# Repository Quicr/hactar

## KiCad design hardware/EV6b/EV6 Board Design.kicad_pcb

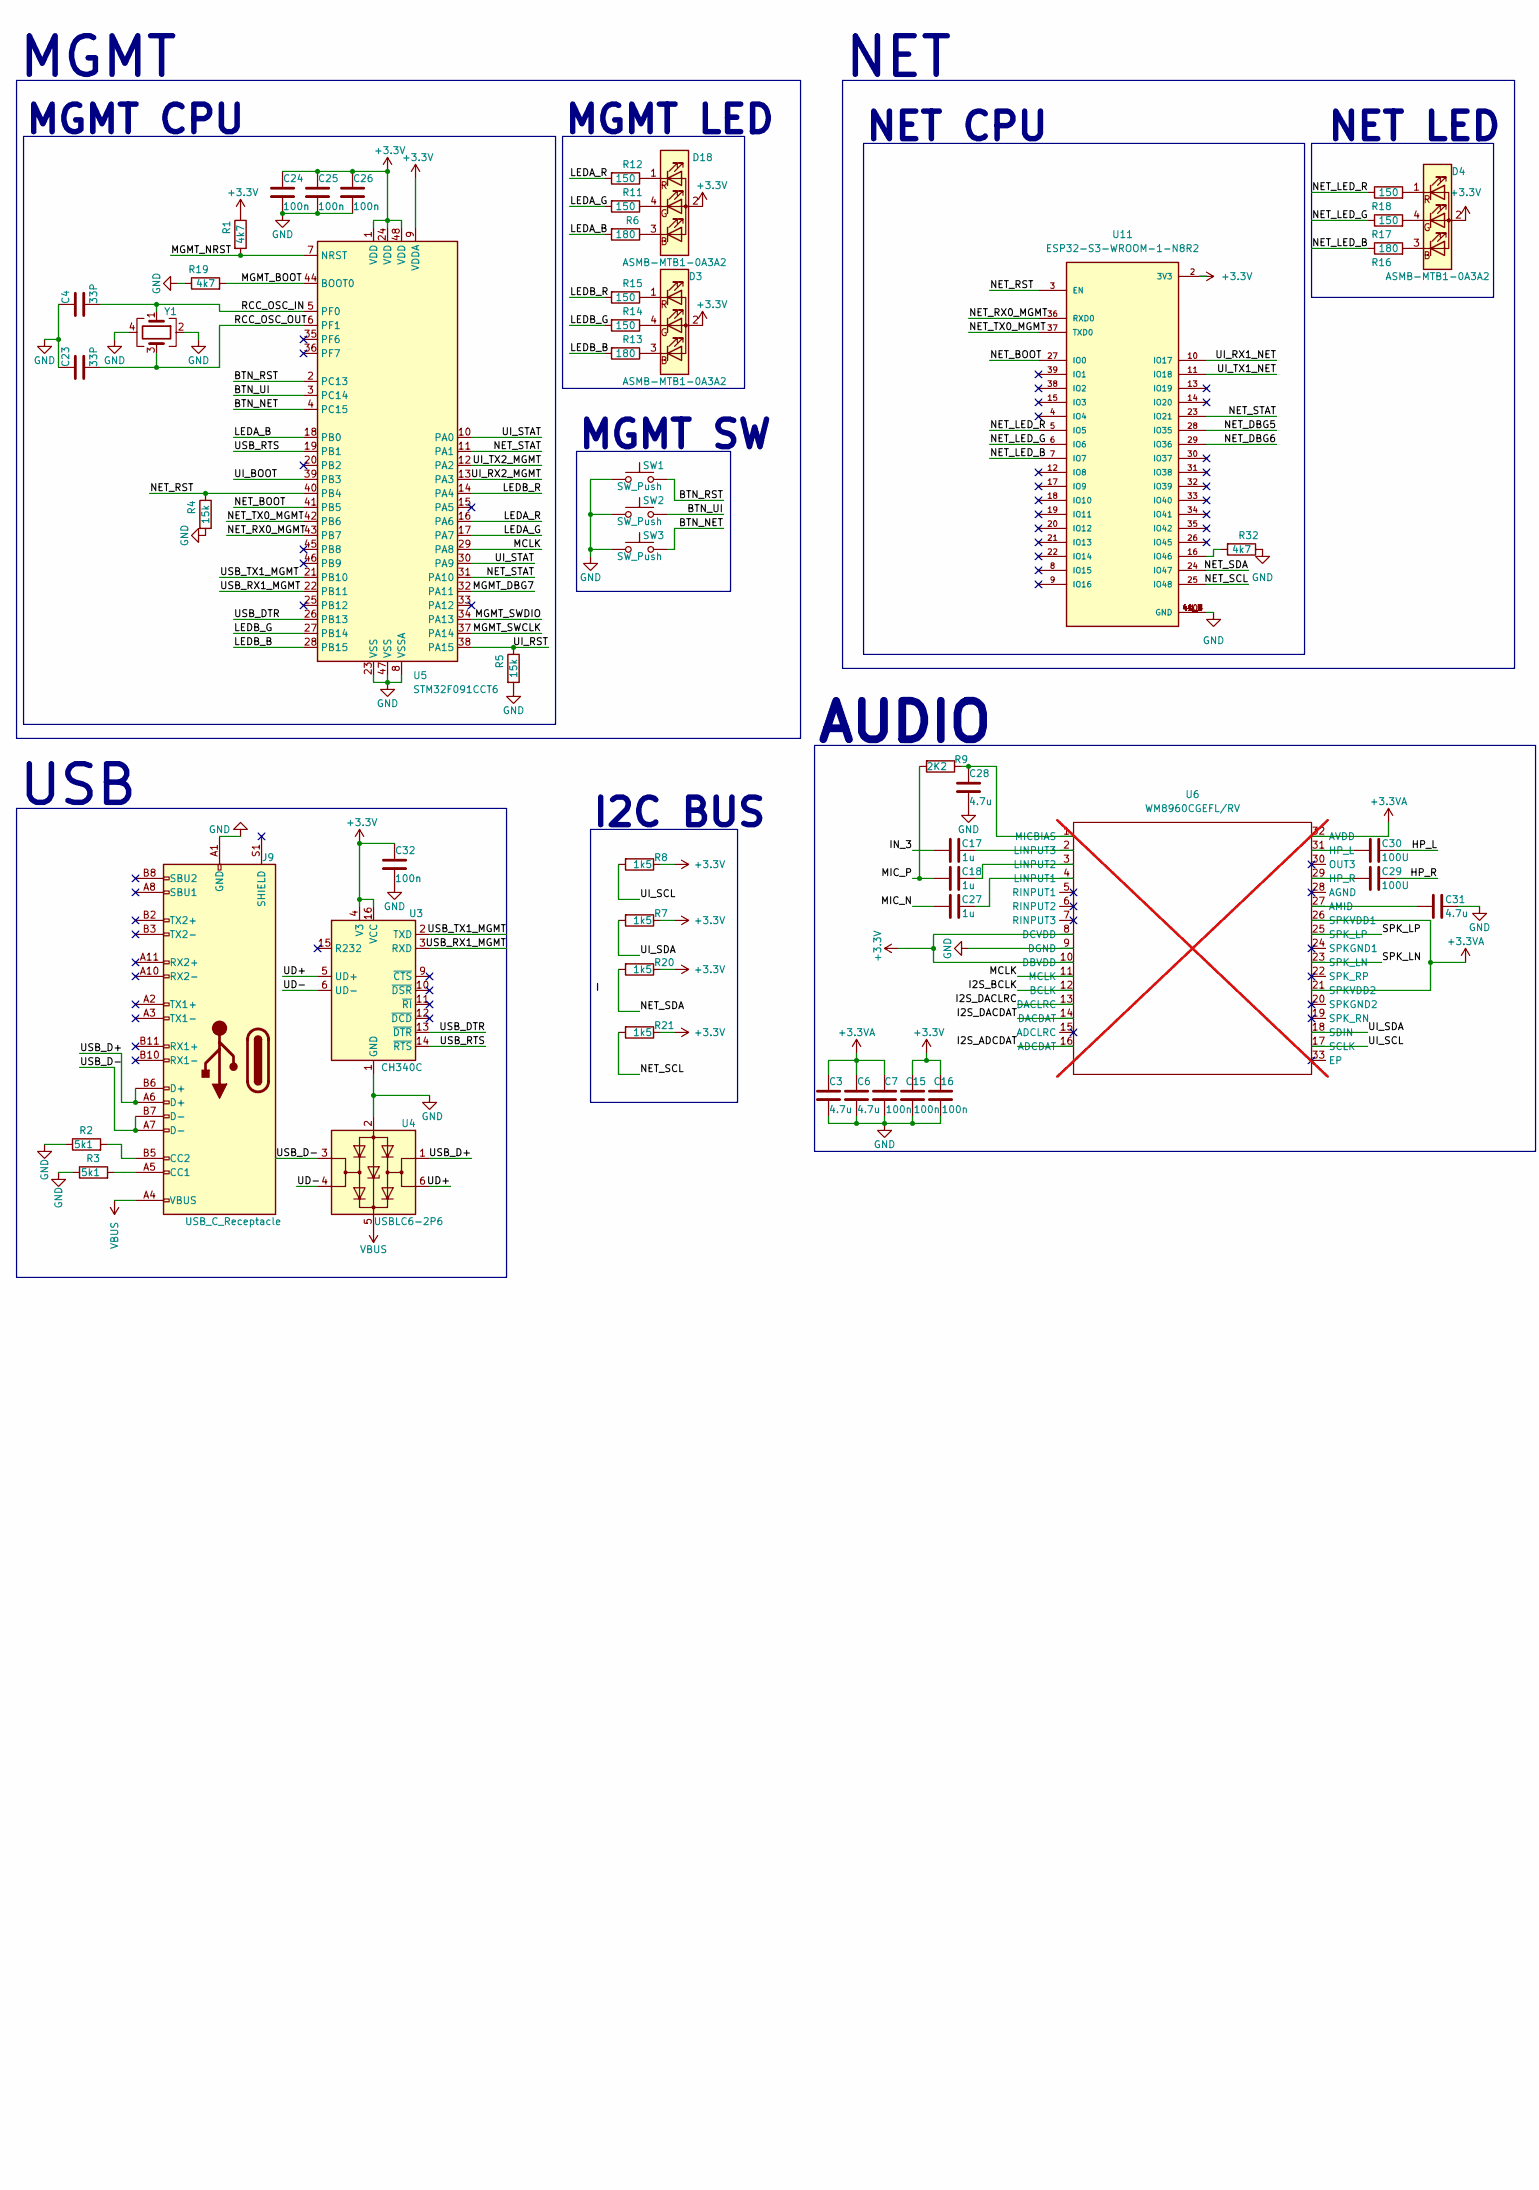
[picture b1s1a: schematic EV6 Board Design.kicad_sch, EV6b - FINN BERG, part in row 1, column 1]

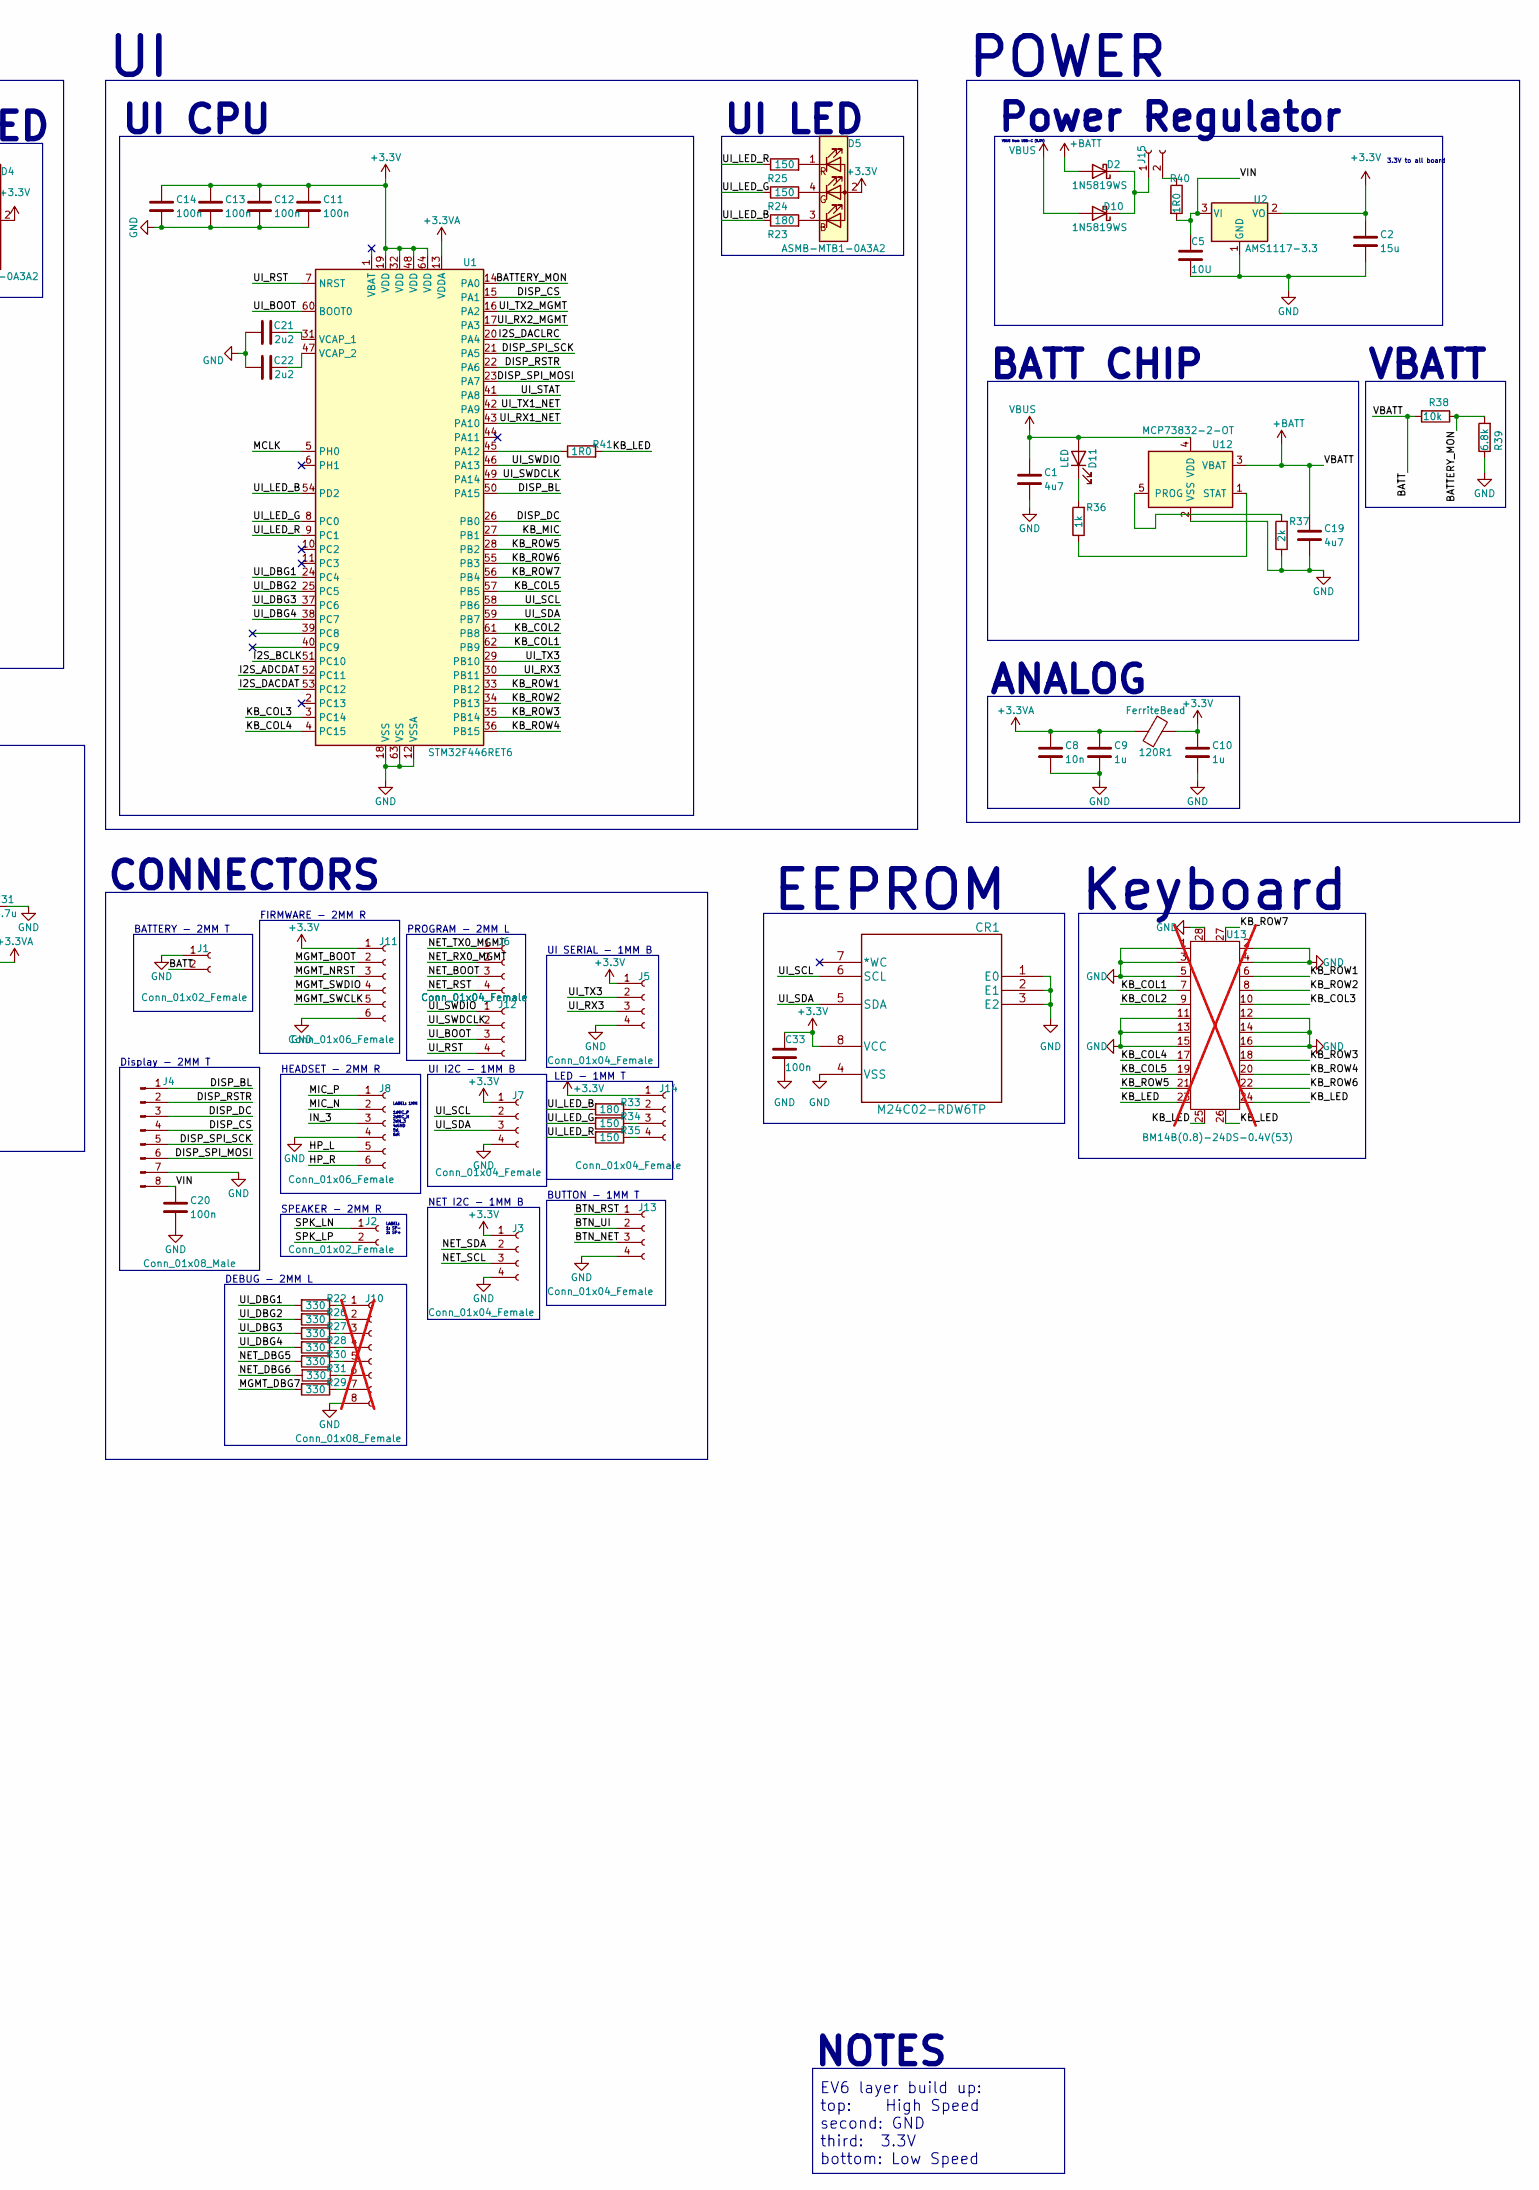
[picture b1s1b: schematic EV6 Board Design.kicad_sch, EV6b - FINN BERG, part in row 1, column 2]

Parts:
120R1: FerriteBead; L_0603_1608Metric
C1, C19: 4u7; C_0402_1005Metric
C2: 15u; C_0402_1005Metric
C3, C6, C28, C31: 4.7u; C_0402_1005Metric
C4, C23: 33P; C_0805_2012Metric
C5: 10U; C_0402_1005Metric
C7, C11, C12, C13, C14, C15, C16, C20, C24, C25, C26, C32, C33: 100n; C_0402_1005Metric
C8: 10n; C_0402_1005Metric
C9, C10, C17, C18, C27: 1u; C_0402_1005Metric
C21, C22: 2u2; C_0402_1005Metric
C29, C30: 100U; C_1206_3216Metric
CR1: M24C02-RDW6TP; New_ESP32_M24C02-RMN6TP
D2, D10: 1N5819WS; D_SOD-323
D3, D4, D5, D18: ASMB-MTB1-0A3A2; LED RGB
D11: LED; LED_0805_2012Metric
J1, J2, J15: Conn_01x02_Female; JST_PH_S2B-PH-SM4-TB_1x02-1MP_P2.00mm_Horizontal
J3, J5, J6, J7, J12, J13, J14: Conn_01x04_Female; 1x4pin 1mm connector
J4: Conn_01x08_Male; PinHeader_1x08_P2.54mm_Vertical
J8, J11: Conn_01x06_Female; JST_PH_S6B-PH-SM4-TB_1x06-1MP_P2.00mm_Horizontal
J9: USB_C_Receptacle; USB_C_Receptacle_HRO_TYPE-C-31-M-12
J10: Conn_01x08_Female; JST_PH_S8B-PH-SM4-TB_1x08-1MP_P2.00mm_Horizontal; not fitted
R1, R19, R32: 4k7; R_0402_1005Metric
R2, R3: 5k1; R_0402_1005Metric
R4, R5: 15k; R_0402_1005Metric
R6, R13, R16, R23, R33: 180; R_0402_1005Metric
R7, R8, R20, R21: 1k5; R_0402_1005Metric
R9: 2K2; R_0402_1005Metric
R11, R12, R14, R15, R17, R18, R24, R25, R34, R35: 150; R_0402_1005Metric
R22, R26, R27, R28, R29, R30, R31: 330; R_0402_1005Metric
R36: 1k; R_0402_1005Metric
R37: 2k; R_0402_1005Metric
R38: 10k; R_0402_1005Metric
R39: 6.8k; R_0402_1005Metric
R40, R41: 1R0; R_0402_1005Metric
SW1, SW2, SW3: SW_Push; SW_DIP_SPSTx01_Slide_6.7x4.1mm_W6.73mm_P2.54mm_LowProfile_J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
U1: STM32F446RET6; LQFP-64_10x10mm_P0.5mm
U2: AMS1117-3.3; SOT-223-3_TabPin2
U3: CH340C; SOIC-16_3.9x9.9mm_P1.27mm
U4: USBLC6-2P6; SOT-666
U5: STM32F091CCT6; LQFP-48_7x7mm_P0.5mm; LCSC C129795
U6: WM8960CGEFL/RV; QFN50P500X500X90-33N; not fitted
U11: ESP32-S3-WROOM-1-N8R2; ESP32-S3-WROOM-1U
U12: MCP73832-2-OT; SOT-23-5
U13: BM14B(0.8)-24DS-0.4V(53); not fitted
Y1: Crystal_GND24; Crystal_SMD_3225-4Pin_3.2x2.5mm

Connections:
+3.3V: 120R1.2, C2.1, C10.1, C11.1, C12.1, C13.1, C14.1, C15.2, C16.2, C24.1, C25.1, C26.1, C32.1, C33.1, CR1.8 (VCC), D3.2 (A), D4.2 (A), D5.2 (A), D18.2 (A), J3.1, J5.1, J7.1, J11.1, J14.1, R1.1, R7.1, R8.1, R20.1, R21.1, U1.19 (VDD), U1.32 (VDD), U1.48 (VDD), U1.64 (VDD), U2.2 (VO), U3.4 (V3), U3.16 (VCC), U5.1 (VDD), U5.9 (VDDA), U5.24 (VDD), U5.48 (VDD), U6.8 (DCVDD), U6.10 (DBVDD), U11.2 (3V3)
+3.3VA: 120R1.1, C3.1, C6.1, C7.2, C8.1, C9.1, U1.13 (VDDA), U6.21 (SPKVDD2), U6.26 (SPKVDD1), U6.32 (AVDD)
+BATT: C19.1, D2.2 (A), J1.2, R38.2, U12.3 (VBAT)
/BATTERY_MON: R38.1, R39.2, U1.14 (PA0)
/BTN_NET: J13.3, SW3.1, U5.4 (PC15)
/BTN_RST: J13.1, SW1.1, U5.2 (PC13)
/BTN_UI: J13.2, SW2.1, U5.3 (PC14)
/DISP_BL: J4.1, U1.50 (PA15)
/DISP_CS: J4.4, U1.15 (PA1)
/DISP_DC: J4.3, U1.26 (PB0)
/DISP_RSTR: J4.2, U1.22 (PA6)
/DISP_SPI_MOSI: J4.6, U1.23 (PA7)
/DISP_SPI_SCK: J4.5, U1.21 (PA5)
/HP_L: C30.2, J8.5
/HP_R: C29.2, J8.6
/I2S_ADCDAT: U1.52 (PC11), U6.16 (ADCDAT)
/I2S_BCLK: U1.51 (PC10), U6.12 (BCLK)
/I2S_DACDAT: U1.53 (PC12), U6.14 (DACDAT)
/I2S_DACLRC: U1.20 (PA4), U6.13 (DACLRC)
/IN_3: C17.1, J8.3
/KB_COL1: U1.62 (PB9), U13.7
/KB_COL2: U1.61 (PB8), U13.9
/KB_COL3: U1.3 (PC14), U13.10
/KB_COL4: U1.4 (PC15), U13.17
/KB_COL5: U1.57 (PB5), U13.19
/KB_LED: R41.2, U13.23, U13.24, U13.25, U13.26
/KB_MIC: U1.27 (PB1)
/KB_ROW1: U1.33 (PB12), U13.6
/KB_ROW2: U1.34 (PB13), U13.8
/KB_ROW3: U1.35 (PB14), U13.18
/KB_ROW4: U1.36 (PB15), U13.20
/KB_ROW5: U1.28 (PB2), U13.21
/KB_ROW6: U1.55 (PB3), U13.22
/KB_ROW7: U1.56 (PB4), U13.27
/LEDA_B: R6.2, U5.18 (PB0)
/LEDA_G: R11.2, U5.17 (PA7)
/LEDA_R: R12.2, U5.16 (PA6)
/LEDB_B: R13.2, U5.28 (PB15)
/LEDB_G: R14.2, U5.27 (PB14)
/LEDB_R: R15.2, U5.14 (PA4)
/MCLK: U1.5 (PH0), U5.29 (PA8), U6.11 (MCLK)
/MGMT_BOOT: J11.2, R19.2, U5.44 (BOOT0)
/MGMT_DBG7: R29.2, U5.32 (PA11)
/MGMT_NRST: J11.3, R1.2, U5.7 (NRST)
/MGMT_SWCLK: J11.5, U5.37 (PA14)
/MGMT_SWDIO: J11.4, U5.34 (PA13)
/MIC_N: C27.1, J8.2
/MIC_P: C18.1, J8.1, R9.2
/NET_BOOT: J6.3, U5.41 (PB5), U11.27 (IO0)
/NET_DBG5: R30.2, U11.28 (IO35)
/NET_DBG6: R31.2, U11.29 (IO36)
/NET_LED_B: R16.1, U11.7 (IO7)
/NET_LED_G: R17.1, U11.6 (IO6)
/NET_LED_R: R18.1, U11.5 (IO5)
/NET_RST: J6.4, R4.1, U5.40 (PB4), U11.3 (EN)
/NET_RX0_MGMT: J6.2, U5.43 (PB7), U11.36 (RXD0)
/NET_SCL: J3.3, R21.2, U11.25 (IO48)
/NET_SDA: J3.2, R20.2, U11.24 (IO47)
/NET_STAT: U5.11 (PA1), U5.31 (PA10), U11.23 (IO21)
/NET_TX0_MGMT: J6.1, U5.42 (PB6), U11.37 (TXD0)
/RCC_OSC_IN: C4.2, U5.5 (PF0), Y1.1
/RCC_OSC_OUT: C23.2, U5.6 (PF1), Y1.3
/SPK_LN: J2.1, U6.23 (SPK_LN)
/SPK_LP: J2.2, U6.25 (SPK_LP)
/UD+: U3.5 (UD+), U4.6 (I/O1)
/UD-: U3.6 (UD-), U4.4 (I/O2)
/UI_BOOT: J12.3, U1.60 (BOOT0), U5.39 (PB3)
/UI_DBG1: R22.2, U1.24 (PC4)
/UI_DBG2: R26.2, U1.25 (PC5)
/UI_DBG3: R27.2, U1.37 (PC6)
/UI_DBG4: R28.2, U1.38 (PC7)
/UI_LED_B: R23.1, R33.2, U1.54 (PD2)
/UI_LED_G: R24.1, R34.2, U1.8 (PC0)
/UI_LED_R: R25.1, R35.2, U1.9 (PC1)
/UI_RST: J12.4, R5.1, U1.7 (NRST), U5.38 (PA15)
/UI_RX1_NET: U1.43 (PA10), U11.10 (IO17)
/UI_RX2_MGMT: U1.17 (PA3), U5.13 (PA3)
/UI_RX3: J5.3, U1.30 (PB11)
/UI_SCL: CR1.6 (SCL), J7.2, R8.2, U1.58 (PB6), U6.17 (SCLK)
/UI_SDA: CR1.5 (SDA), J7.3, R7.2, U1.59 (PB7), U6.18 (SDIN)
/UI_STAT: U1.41 (PA8), U5.10 (PA0), U5.30 (PA9)
/UI_SWDCLK: J12.2, U1.49 (PA14)
/UI_SWDIO: J12.1, U1.46 (PA13)
/UI_TX1_NET: U1.42 (PA9), U11.11 (IO18)
/UI_TX2_MGMT: U1.16 (PA2), U5.12 (PA2)
/UI_TX3: J5.2, U1.29 (PB10)
/USB_D+: J9.A6 (D+), J9.B6 (D+), U4.1 (I/O1)
/USB_D-: J9.A7 (D-), J9.B7 (D-), U4.3 (I/O2)
/USB_DTR: U3.13 (~DTR), U5.26 (PB13)
/USB_RTS: U3.14 (~RTS), U5.19 (PB1)
/USB_RX1_MGMT: U3.3 (RXD), U5.22 (PB11)
/USB_TX1_MGMT: U3.2 (TXD), U5.21 (PB10)
/VIN: C5.1, C20.1, J4.8, R40.2, U2.3 (VI)
GND: C1.2, C2.2, C3.2, C4.1, C5.2, C6.2, C7.1, C8.2, C9.2, C10.2, C11.2, C12.2, C13.2, C14.2, C15.1, C16.1, C19.2, C20.2, C21.1, C22.1, C23.1, C24.2, C25.2, C26.2, C28.2, C31.1, C32.2, C33.2, CR1.1 (E0), CR1.2 (E1), CR1.3 (E2), CR1.4 (VSS), J1.1, J3.4, J4.7, J5.4, J7.4, J8.4, J9.A1 (GND), J9.A12 (GND), J9.B1 (GND), J9.B12 (GND), J10.8, J11.6, J13.4, R2.1, R3.1, R4.2, R5.2, R19.1, R32.1, R37.1, R39.1, SW1.2, SW2.2, SW3.2, U1.12 (VSSA), U1.18 (VSS), U1.63 (VSS), U2.1 (GND), U3.1 (GND), U4.2 (GND), U5.8 (VSSA), U5.23 (VSS), U5.47 (VSS), U6.9 (DGND), U11.1 (GND), U11.40 (GND), U11.41_1 (GND), U11.41_2 (GND), U11.41_3 (GND), U11.41_4 (GND), U11.41_5 (GND), U11.41_6 (GND), U11.41_7 (GND), U11.41_8 (GND), U11.41_9 (GND), U12.2 (VSS), U13.1, U13.2, U13.3, U13.4, U13.5, U13.11, U13.12, U13.13, U13.14, U13.15, U13.16, U13.28, Y1.2, Y1.4
unnamed: D3.3 (BK), R13.1
unnamed: D3.4 (GK), R14.1
unnamed: D3.1 (RK), R15.1
unnamed: D4.3 (BK), R16.2
unnamed: D4.4 (GK), R17.2
unnamed: D4.1 (RK), R18.2
unnamed: D5.3 (BK), R23.2
unnamed: D5.4 (GK), R24.2
unnamed: D5.1 (RK), R25.2
unnamed: D2.1 (K), D10.1 (K), J15.1
unnamed: D11.1 (K), R36.2
unnamed: D18.3 (BK), R6.1
unnamed: D18.4 (GK), R11.1
unnamed: D18.1 (RK), R12.1
unnamed: J9.A5 (CC1), R3.2
unnamed: J9.B5 (CC2), R2.2
unnamed: J10.1, R22.1
unnamed: J10.2, R26.1
unnamed: J10.3, R27.1
unnamed: J10.4, R28.1
unnamed: J10.5, R30.1
unnamed: J10.6, R31.1
unnamed: J10.7, R29.1
unnamed: J14.2, R33.1
unnamed: J14.3, R34.1
unnamed: J14.4, R35.1
unnamed: J15.2, R40.1
unnamed: R41.1, U1.45 (PA12)
unnamed: C21.2, U1.31 (VCAP_1)
unnamed: C22.2, U1.47 (VCAP_2)
unnamed: C31.2, U6.27 (AMID)
unnamed: C30.1, U6.31 (HP_L)
unnamed: C29.1, U6.29 (HP_R)
unnamed: C27.2, U6.4 (LINPUT1)
unnamed: C18.2, U6.3 (LINPUT2)
unnamed: C17.2, U6.2 (LINPUT3)
unnamed: C28.1, R9.1, U6.1 (MICBIAS)
unnamed: R32.2, U11.16 (IO46)
unnamed: R37.2, U12.5 (PROG)
unnamed: R36.1, U12.1 (STAT)
VBUS: C1.1, D10.2 (A), D11.2 (A), J9.A4 (VBUS), J9.A9 (VBUS), J9.B4 (VBUS), J9.B9 (VBUS), U4.5 (VBUS), U12.4 (VDD)

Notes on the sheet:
MGMT
VBATT
SPEAKER - 2MM R
NET CPU
MGMT CPU
BATT CHIP
NET
POWER
PROGRAM - 2MM L
CONNECTORS
3.3V to all board
NET LED
UI CPU
HEADSET - 2MM R
BATTERY - 2MM T
BUTTON - 1MM T
EV6 layer build up: top: High Speed second: GND third: 3.3V bottom: Low Speed
LABEL: 1MM 1:MIC_P 2:MIC_N 3:IN_3 4:GND 5:L 6:R
AUDIO
MGMT SW
UI SERIAL - 1MM B
EEPROM
UI I2C - 1MM B
I2C BUS
FIRMWARE - 2MM R
USB
VBUS from USB-C (5.0V)
MGMT LED
LABEL: 1: SP- 2: SP+
LED - 1MM T
NOTES
Power Regulator
Keyboard
Display - 2MM T
DEBUG - 2MM L
UI LED
NET I2C - 1MM B
ANALOG

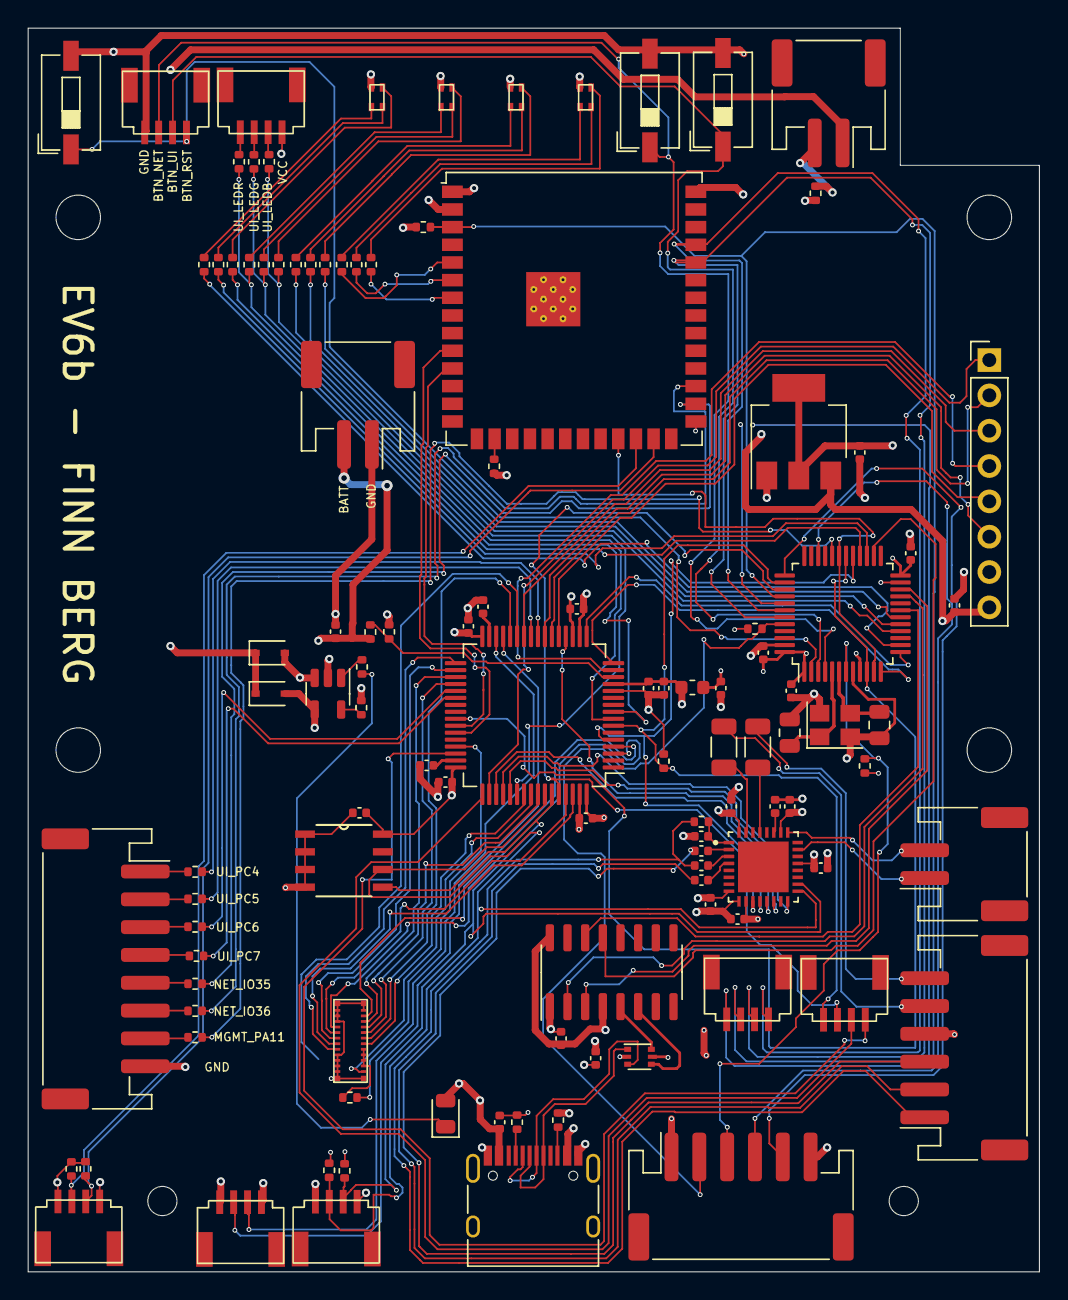
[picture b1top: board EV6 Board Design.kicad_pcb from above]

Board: 4 copper layers, 72.7 x 89.4 mm, 110 parts (0 on the bottom side), 134 nets.

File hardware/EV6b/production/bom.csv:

Designator,Footprint,Quantity,Value,LCSC Part #
120R1,0603,1,FerriteBead,C127301
"C1, C19, C28, C3, C31, C6",0402,6,4u7,C23733
"C10, C17, C18, C27, C9",0402,5,1u,C142376
"C11, C12, C13, C14, C15, C16, C20, C24, C25, C26, C32, C33, C7",0402,13,100n,C338032
C2,0402,1,15u,C703069
"C21, C22",0402,2,2u2,C76594
"C23, C4",0805,2,33p,C1663
"C29, C30",1206,2,100u,C87164
C5,0402,1,10U,C87148
C8,0402,1,10n,C361206
CR1,New_ESP32_M24C02-RMN6TP,1,M24C02-RDW6TP,C83836
"D10, D2",D_SOD-323,2,1N5819WS,C191023
D11,0805,1,LED,C130114
"D18, D3, D4, D5",LED RGB,4,ASMB-MTB1-0A3A2,C2927824
"J1, J15, J2",JST_PH_S2B-PH-SM4-TB_1x02-1MP_P2.00mm_Horizontal,3,Conn_01x02_Female,C295747
"J11, J8",JST_PH_S6B-PH-SM4-TB_1x06-1MP_P2.00mm_Horizontal,2,Conn_01x06_Female,C265405
"J12, J13, J14, J3, J5, J6, J7",1x4pin 1mm connector,7,Conn_01x04_Female,C3029343
J9,USB_C_Receptacle_HRO_TYPE-C-31-M-12,1,USB_C_Receptacle,C165948
"R1, R19, R32",0402,3,4k7,C82453
"R11, R12, R14, R15, R17, R18, R24, R25, R34, R35",0402,10,150r,C186306
"R13, R16, R23, R33, R6",0402,5,180r,C186119
"R2, R3",0402,2,5k1,C325521
"R20, R21, R7, R8",0402,4,1k5,C144053
"R22, R26, R27, R28, R29, R30, R31",0402,7,330r,C105876
R36,0402,1,1k,C279981
R37,0402,1,2k,C258126
R38,0402,1,10k,C409612
R39,0402,1,6.8k,C131617
"R4, R5",0402,2,15k,C409670
"R40, R41",0402,2,1r0,C881335
R9,0402,1,2K2,C102890
"SW1, SW2, SW3",SW_DIP_SPSTx01_Slide_6.7x4.1mm_W6.73mm_P2.54mm_LowProfile_JPin,3,SW_Push,C266189
U1,LQFP-64_10x10mm_P0.5mm,1,STM32F446RET6,C69336
U11,ESP32-S3-WROOM-1U,1,ESP32-S3-WROOM-1-N8R2,C3013944
U12,SOT-23-5,1,MCP73832-2-OT,C424093
U2,SOT-223-3_TabPin2,1,AMS1117-3.3,C351784
U3,SOIC-16_3.9x9.9mm_P1.27mm,1,CH340C,C84681
U4,SOT-666,1,USBLC6-2P6,C2827693
U5,LQFP-48_7x7mm_P0.5mm,1,STM32F091CCT6,C129795
Y1,Crystal_SMD_3225-4Pin_3.2x2.5mm,1,Crystal_GND24,C13738

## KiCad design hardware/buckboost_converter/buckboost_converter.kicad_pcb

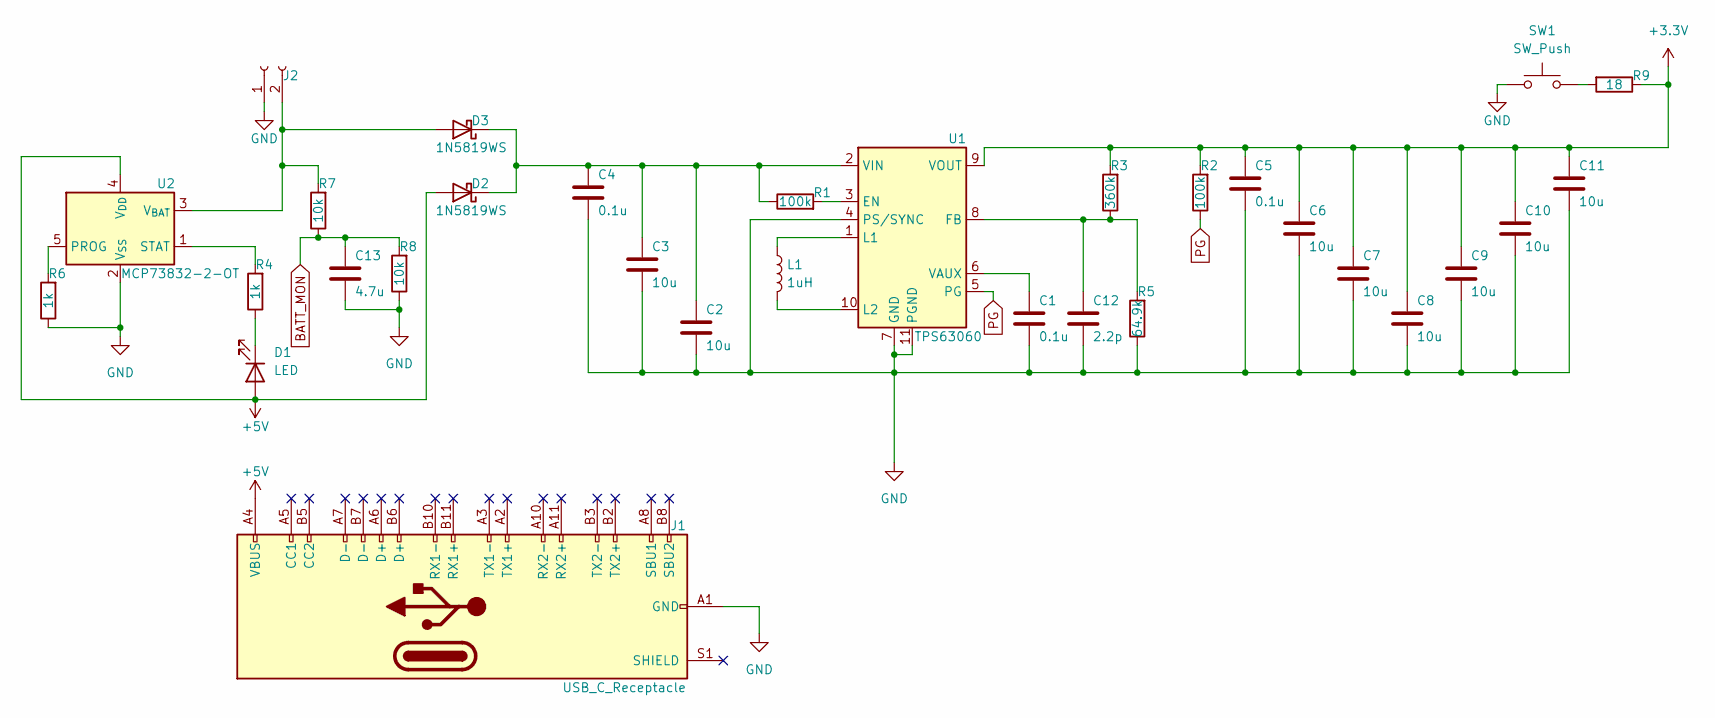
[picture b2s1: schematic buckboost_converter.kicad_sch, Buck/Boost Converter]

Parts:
C1, C4, C5: 0.1u; C_0805_2012Metric
C2, C3, C6, C7, C8, C9, C10, C11: 10u; C_0805_2012Metric
C12: 2.2p; C_0805_2012Metric
C13: 4.7u; C_0805_2012Metric
D1: LED; D_0805_2012Metric
D2, D3: 1N5819WS; D_SOD-323
J1: USB_C_Receptacle; USB_C_Receptacle_HRO_TYPE-C-31-M-12
J2: Conn_01x02_Socket; JST_PH_S2B-PH-SM4-TB_1x02-1MP_P2.00mm_Horizontal
L1: 1uH; L_1806_4516Metric
R1, R2: 100k; R_0402_1005Metric
R3: 360k; R_0402_1005Metric
R4, R6: 1k; R_0402_1005Metric
R5: 64.9k; R_0402_1005Metric
R7, R8: 10k; R_0402_1005Metric
R9: 18; R_1218_3246Metric
SW1: SW_Push; SW_DIP_SPSTx01_Slide_6.7x4.1mm_W6.73mm_P2.54mm_LowProfile_J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
U1: TPS63060; Texas_S-PWSON-N10_ThermalVias
U2: MCP73832-2-OT; SOT-23-5

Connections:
+3.3V: C5.1, C6.1, C7.1, C8.1, C9.1, C10.1, C11.1, R2.2, R3.2, R9.1, U1.9 (VOUT)
+5V: D1.2 (A), D2.2 (A), J1.A4 (VBUS), J1.A9 (VBUS), J1.B4 (VBUS), J1.B9 (VBUS), U2.4 (V_{DD})
BATT_MON: C13.1, R7.1, R8.2
GND: C1.2, C2.2, C3.2, C4.2, C5.2, C6.2, C7.2, C8.2, C9.2, C10.2, C11.2, C12.2, C13.2, J1.A1 (GND), J1.A12 (GND), J1.B1 (GND), J1.B12 (GND), J2.1, R5.1, R6.1, R8.1, SW1.1, U1.4 (PS/SYNC), U1.7 (GND), U1.11 (PGND), U2.2 (V_{SS})
unnamed: D1.1 (K), R4.1
unnamed: C2.1, C3.1, C4.1, D2.1 (K), D3.1 (K), R1.1, U1.2 (VIN)
unnamed: D3.2 (A), J2.2, R7.2, U2.3 (V_{BAT})
unnamed: R9.2, SW1.2
unnamed: R1.2, U1.3 (EN)
unnamed: C12.1, R3.1, R5.2, U1.8 (FB)
unnamed: L1.1, U1.1 (L1)
unnamed: L1.2, U1.10 (L2)
unnamed: C1.1, U1.6 (VAUX)
unnamed: R6.2, U2.5 (PROG)
unnamed: R4.2, U2.1 (STAT)
PG: R2.1, U1.5 (PG)

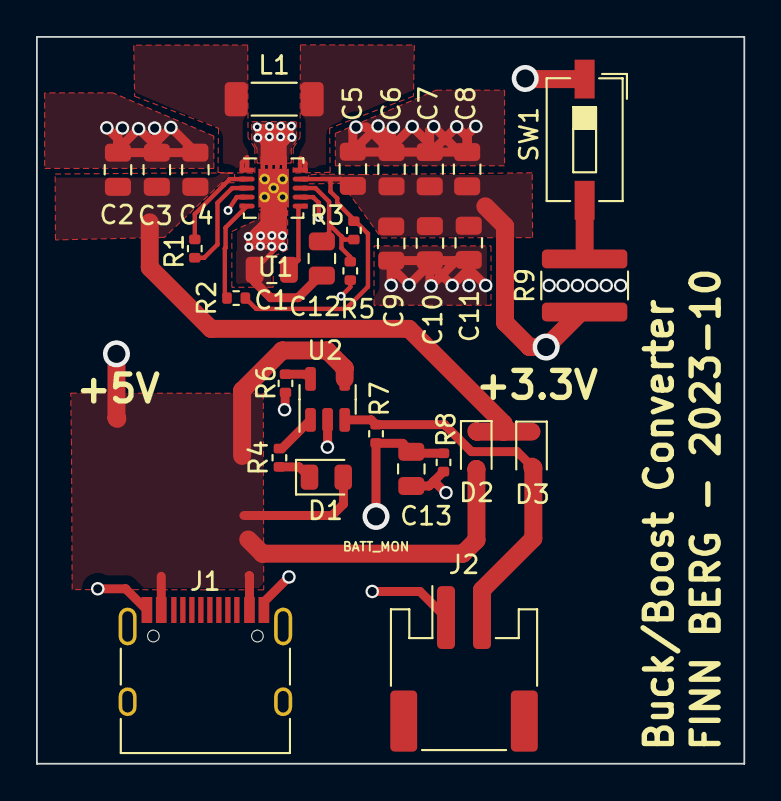
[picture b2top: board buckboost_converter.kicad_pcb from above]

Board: 2 copper layers, 39.3 x 40.4 mm, 31 parts (0 on the bottom side), 16 nets.
